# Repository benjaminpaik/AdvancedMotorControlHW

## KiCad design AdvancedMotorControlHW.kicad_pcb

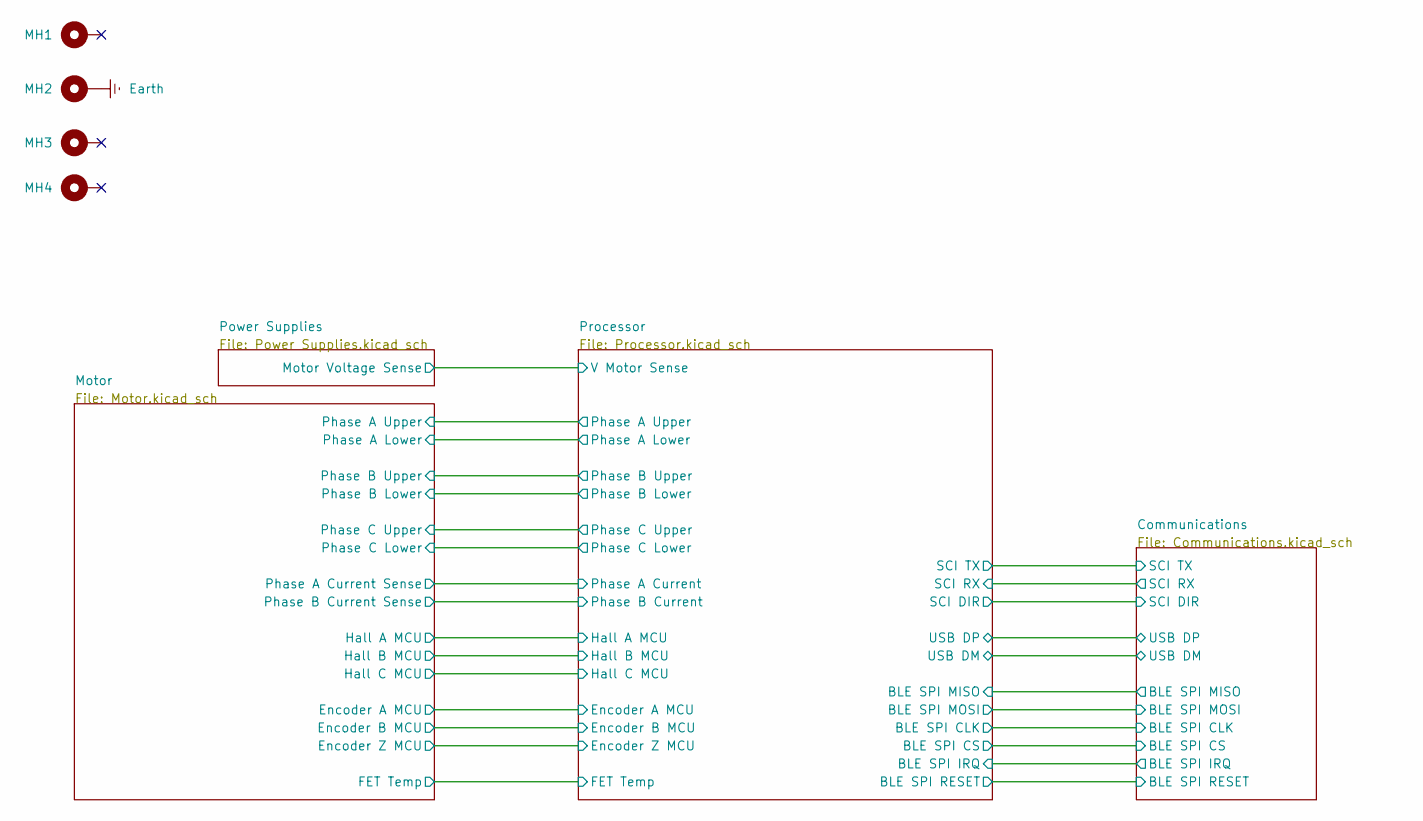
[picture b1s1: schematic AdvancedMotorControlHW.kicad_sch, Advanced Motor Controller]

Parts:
MH1, MH3, MH4: MountingHole; MountingHole_3.2mm_M3_Pad; Manufacturer Part Number 3480
MH2: MountingHole_Pad; MountingHole_3.2mm_M3_Pad; Manufacturer Part Number 3480

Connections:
Earth: MH2.1; also elsewhere on the board

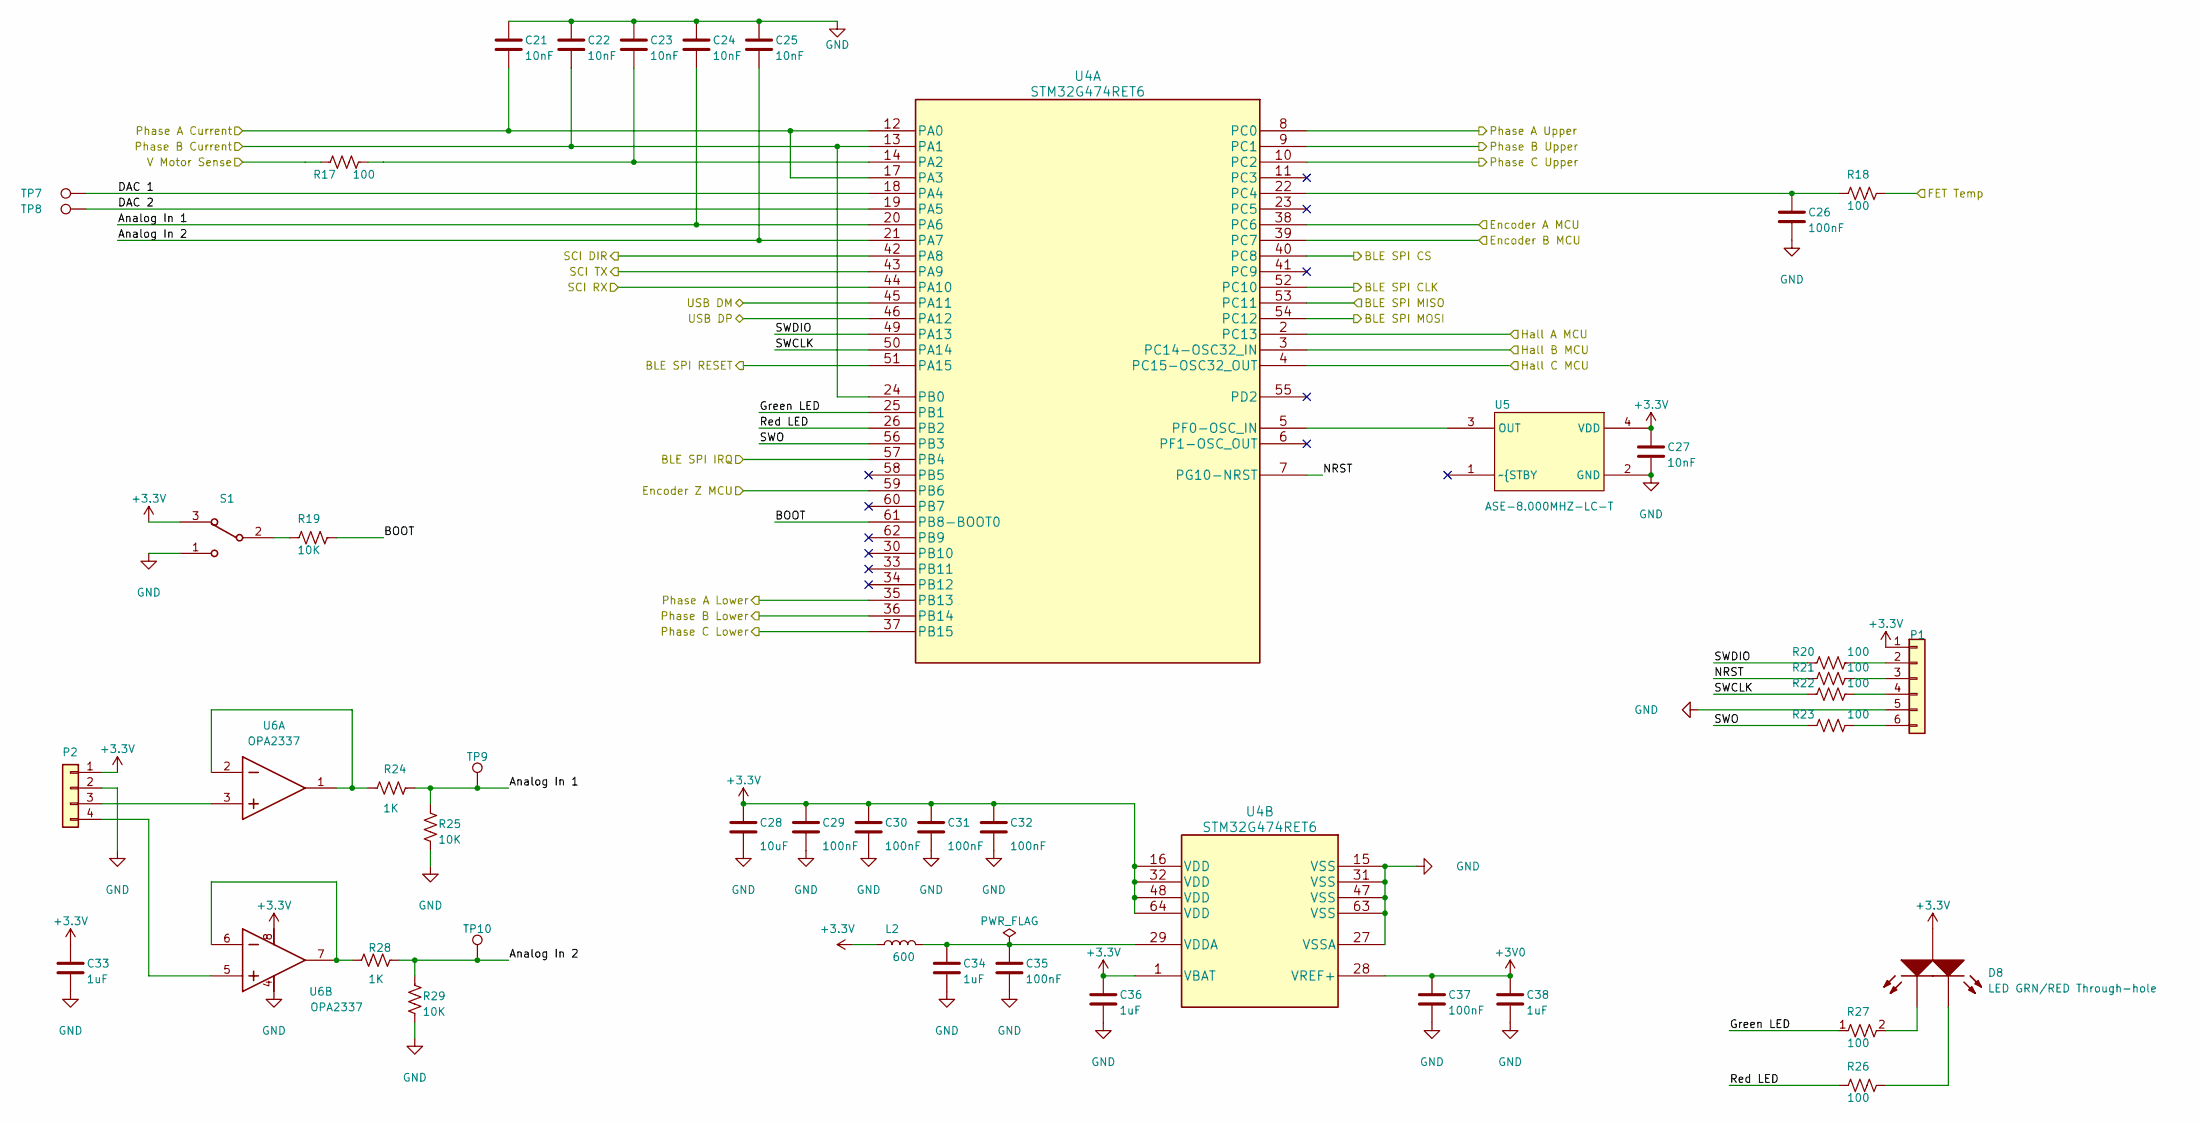
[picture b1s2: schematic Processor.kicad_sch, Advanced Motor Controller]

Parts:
C21, C22, C23, C24, C25, C27: 10nF; C_0603_1608Metric; Manufacturer Part Number CL10B103KB8NCNC
C26, C29, C30, C31, C32, C35, C37: 100nF; C_0603_1608Metric; Manufacturer Part Number 06035G104ZAT2A
C28: 10uF; C_1206_3216Metric; Manufacturer Part Number GRT31CR61H106ME01L
C33, C34, C36, C38: 1uF; C_0603_1608Metric; Manufacturer Part Number CL10A105KA8NNNC
D8: LED GRN/RED Through-hole; LED_D5.0mm-3; Manufacturer Part Number SSL-LX3059IGW-CA
L2: 600; L_0603_1608Metric; Manufacturer Part Number 742792651
P1: TC2030-MCP
P2: MOLEX RIGHT ANGLE HDR1X4; Manufacturer Part Number 0022057048
R17, R18, R20, R21, R22, R23, R26, R27: 100; R_0603_1608Metric; Manufacturer Part Number RC0603FR-07100RL
R19, R25, R29: 10K; R_0805_2012Metric; Manufacturer Part Number RR1220P-103-D
R24, R28: 1K; R_0603_1608Metric; Manufacturer Part Number RR0816P-102-D
S1: JS102011SAQN; Manufacturer Part Number JS102011SAQN
TP7, TP8, TP9, TP10: TestPoint; Manufacturer Part Number 5003
U4: STM32G474RET6; LQFP-64_10x10mm_P0.5mm; Manufacturer Part Number STM32G474RET6
U5: ASE-8.000MHZ-LC-T; Crystal_SMD_Abracon_ABM8G-4Pin_3.2x2.5mm; Manufacturer Part Number ASE-8.000MHZ-LC-T
U6: OPA2337; SOT-23-8; Manufacturer Part Number OPA2337EA/3K

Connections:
+3.3V: C27.1, C28.1, C29.1, C30.1, C31.1, C32.1, C33.1, C36.1, D8.2 (CA), L2.1, P1.1, P2.1, S1.3, U4.1 (VBAT), U4.16 (VDD), U4.32 (VDD), U4.48 (VDD), U4.64 (VDD), U5.4 (VDD), U6.8; also elsewhere on the board
+3V0: C37.1, C38.1, U4.28 (VREF+); also elsewhere on the board
/Communications/BLE SPI CLK: U4.52 (PC10); also elsewhere on the board
/Communications/BLE SPI CS: U4.40 (PC8); also elsewhere on the board
/Communications/BLE SPI IRQ: U4.57 (PB4); also elsewhere on the board
/Communications/BLE SPI MISO: U4.53 (PC11); also elsewhere on the board
/Communications/BLE SPI MOSI: U4.54 (PC12); also elsewhere on the board
/Communications/RESETN: U4.51 (PA15); also elsewhere on the board
/Communications/SCI DIR: U4.42 (PA8); also elsewhere on the board
/Communications/SCI RX: U4.44 (PA10); also elsewhere on the board
/Communications/SCI TX: U4.43 (PA9); also elsewhere on the board
/Communications/USB DM: U4.45 (PA11); also elsewhere on the board
/Communications/USB DP: U4.46 (PA12); also elsewhere on the board
/Motor/Encoder A MCU: U4.38 (PC6); also elsewhere on the board
/Motor/Encoder B MCU: U4.39 (PC7); also elsewhere on the board
/Motor/Encoder Z MCU: U4.59 (PB6); also elsewhere on the board
/Motor/FET Temp: R18.2; also elsewhere on the board
/Motor/Hall A MCU: U4.2 (PC13); also elsewhere on the board
/Motor/Hall B MCU: U4.3 (PC14-OSC32_IN); also elsewhere on the board
/Motor/Hall C MCU: U4.4 (PC15-OSC32_OUT); also elsewhere on the board
/Motor/Phase A Current Sense: C21.2, U4.12 (PA0), U4.17 (PA3); also elsewhere on the board
/Motor/Phase A Lower: U4.35 (PB13); also elsewhere on the board
/Motor/Phase A Upper: U4.8 (PC0); also elsewhere on the board
/Motor/Phase B Current Sense: C22.2, U4.13 (PA1), U4.24 (PB0); also elsewhere on the board
/Motor/Phase B Lower: U4.36 (PB14); also elsewhere on the board
/Motor/Phase B Upper: U4.9 (PC1); also elsewhere on the board
/Motor/Phase C Lower: U4.37 (PB15); also elsewhere on the board
/Motor/Phase C Upper: U4.10 (PC2); also elsewhere on the board
/Power Supplies/Motor Voltage Sense: R17.1; also elsewhere on the board
/Processor/Analog In 1: C24.2, R24.2, R25.2, TP9.1, U4.20 (PA6)
/Processor/Analog In 2: C25.2, R28.1, R29.2, TP10.1, U4.21 (PA7)
/Processor/BOOT: R19.2, U4.61 (PB8-BOOT0)
/Processor/DAC 1: TP7.1, U4.18 (PA4)
/Processor/DAC 2: TP8.1, U4.19 (PA5)
/Processor/Green LED: R27.1, U4.25 (PB1)
/Processor/NRST: R21.1, U4.7 (PG10-NRST)
/Processor/Red LED: R26.1, U4.26 (PB2)
/Processor/SWCLK: R22.1, U4.50 (PA14)
/Processor/SWDIO: R20.1, U4.49 (PA13)
/Processor/SWO: R23.1, U4.56 (PB3)
GND: C21.1, C22.1, C23.1, C24.1, C25.1, C26.2, C27.2, C28.2, C29.2, C30.2, C31.2, C32.2, C33.2, C34.2, C35.2, C36.2, C37.2, C38.2, P1.5, P2.2, R25.1, R29.1, S1.1, U4.15 (VSS), U4.27 (VSSA), U4.31 (VSS), U4.47 (VSS), U4.63 (VSS), U5.2 (GND), U6.4; also elsewhere on the board
unnamed: C34.1, C35.1, L2.2, U4.29 (VDDA)
unnamed: D8.3 (GK), R27.2
unnamed: D8.1 (RK), R26.2
unnamed: P1.2, R20.2
unnamed: P1.3, R21.2
unnamed: P1.4, R22.2
unnamed: P1.6, R23.2
unnamed: P2.3, U6.3 (IN_A+)
unnamed: P2.4, U6.5 (IN_B+)
unnamed: R19.1, S1.2
unnamed: C23.2, R17.2, U4.14 (PA2)
unnamed: C26.1, R18.1, U4.22 (PC4)
unnamed: U4.5 (PF0-OSC_IN), U5.3 (OUT)
unnamed: R24.1, U6.1 (OUT_A), U6.2 (IN_A-)
unnamed: R28.2, U6.6 (IN_B-), U6.7 (OUT_B)

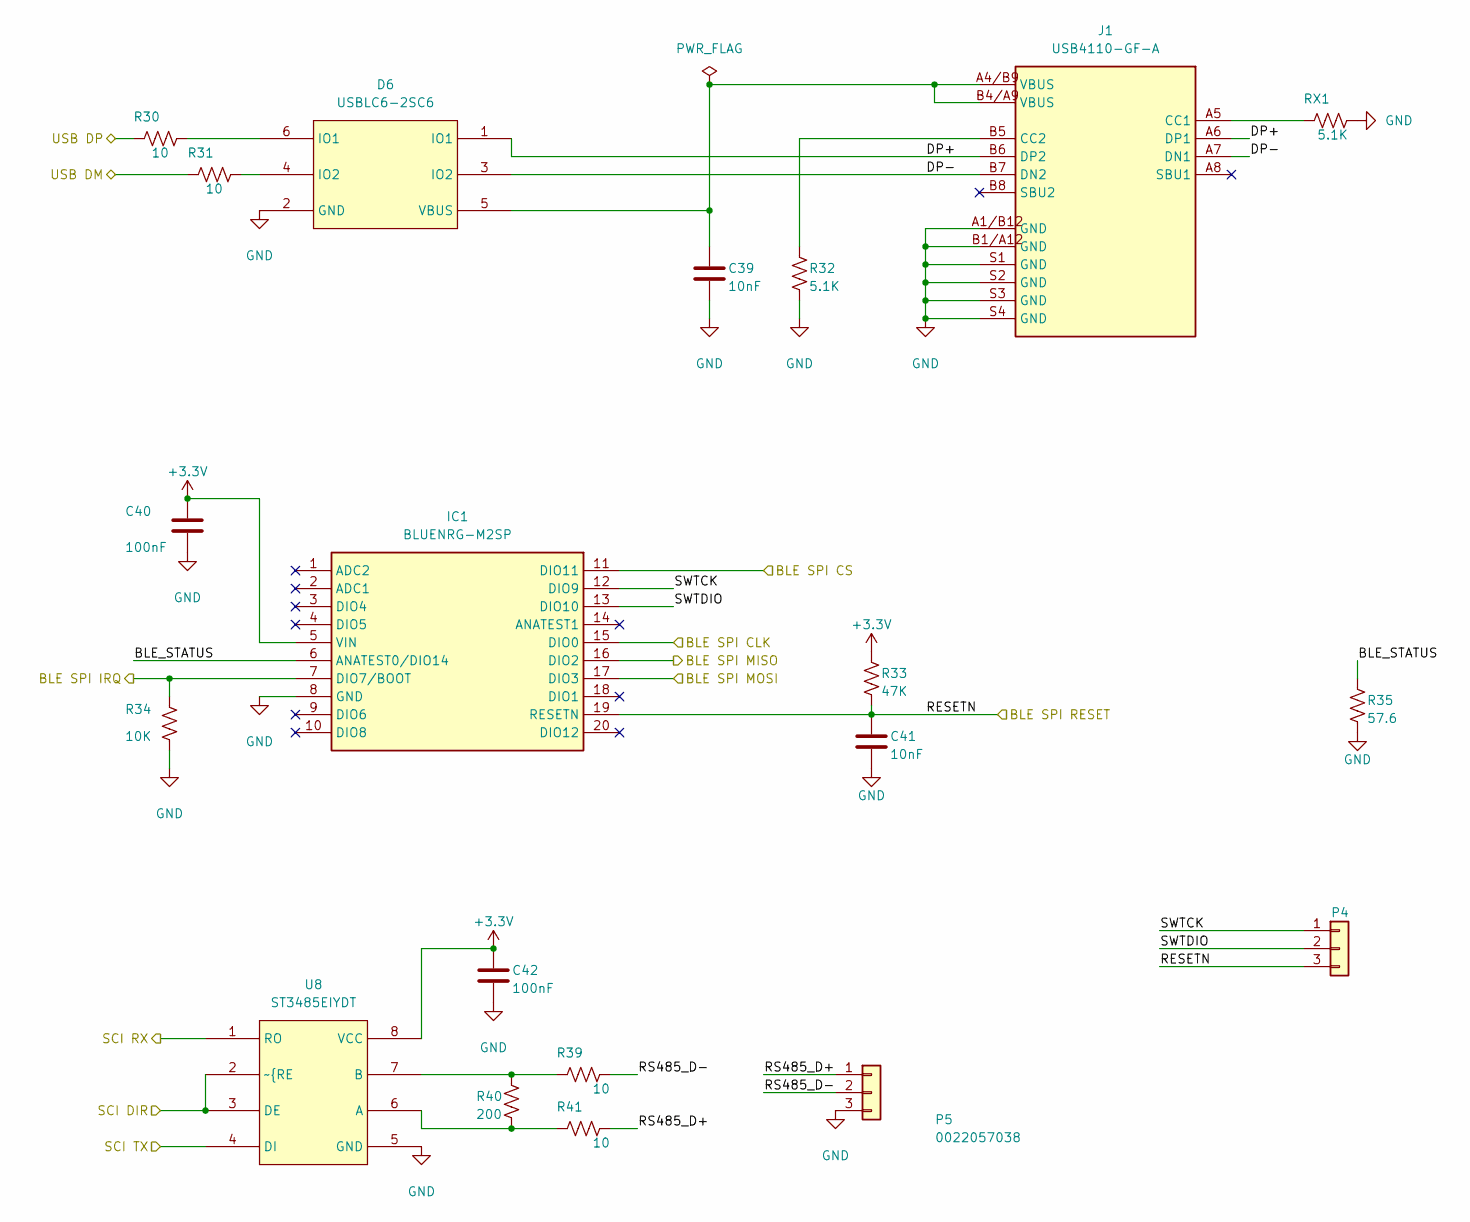
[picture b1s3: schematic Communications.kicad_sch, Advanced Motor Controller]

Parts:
C39, C41: 10nF; C_0603_1608Metric; Manufacturer Part Number CL10B103KB8NCNC
C40, C42: 100nF; C_0603_1608Metric; Manufacturer Part Number 06035G104ZAT2A
D6: USBLC6-2SC6; SOT-23-6; Manufacturer Part Number USBLC6-2SC6
IC1: BLUENRG-M2SP; BLUENRGM2SP; Manufacturer Part Number BLUENRG-M2SP
J1: USB4110-GF-A; USB-C Type 2.0 Connector; Manufacturer Part Number USB4110-GF-A
P4: 0022057038; PinHeader_1x03_P2.54mm_Vertical; Manufacturer Part Number 0022057038
P5: 0022057038; MOLEX RIGHT ANGLE HDR1X3; Manufacturer Part Number 0022057038
R30, R31, R39, R41: 10; R_0603_1608Metric; Manufacturer Part Number CRCW060310R0JNEAC
R32: 5.1K; R_0603_1608Metric; Manufacturer Part Number RMCF0603FT5K10
R33: 47K; R_0603_1608Metric; Manufacturer Part Number RT0603FRD0747KL
R34: 10K; R_0805_2012Metric; Manufacturer Part Number RR1220P-103-D
R35: 57.6; R_0805_2012Metric; Manufacturer Part Number RR1220P-103-D
R40: 200; R_0603_1608Metric; Manufacturer Part Number ERA-3AEB201V
RX1: 5.1K; R_0603_1608Metric; Manufacturer Part Number RMCF0603FT5K10
U8: ST3485EIYDT; SO-8_3.9x4.9mm_P1.27mm; Manufacturer Part Number ST3485EIYDT

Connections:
+3.3V: C40.1, C42.1, IC1.5 (VIN), R33.1, U8.8 (VCC); also elsewhere on the board
/Communications/BLE SPI CLK: IC1.15 (DIO0); also elsewhere on the board
/Communications/BLE SPI CS: IC1.11 (DIO11); also elsewhere on the board
/Communications/BLE SPI IRQ: IC1.7 (DIO7/BOOT), R34.1; also elsewhere on the board
/Communications/BLE SPI MISO: IC1.16 (DIO2); also elsewhere on the board
/Communications/BLE SPI MOSI: IC1.17 (DIO3); also elsewhere on the board
/Communications/BLE_STATUS: IC1.6 (ANATEST0/DIO14), R35.1
/Communications/DP+: D6.1 (IO1), J1.A6 (DP1), J1.B6 (DP2)
/Communications/DP-: D6.3 (IO2), J1.A7 (DN1), J1.B7 (DN2)
/Communications/RESETN: C41.1, IC1.19 (RESETN), P4.3, R33.2; also elsewhere on the board
/Communications/RS485_D+: P5.1, R41.2
/Communications/RS485_D-: P5.2, R39.2
/Communications/SCI DIR: U8.2 (~{RE), U8.3 (DE); also elsewhere on the board
/Communications/SCI RX: U8.1 (RO); also elsewhere on the board
/Communications/SCI TX: U8.4 (DI); also elsewhere on the board
/Communications/SWTCK: IC1.12 (DIO9), P4.1
/Communications/SWTDIO: IC1.13 (DIO10), P4.2
/Communications/USB DM: R31.1; also elsewhere on the board
/Communications/USB DP: R30.1; also elsewhere on the board
GND: C39.2, C40.2, C41.2, C42.2, D6.2 (GND), IC1.8 (GND), J1.A1/B12 (GND), J1.B1/A12 (GND), J1.S1 (GND), J1.S2 (GND), J1.S3 (GND), J1.S4 (GND), P5.3, R32.2, R34.2, R35.2, RX1.2, U8.5 (GND); also elsewhere on the board
unnamed: C39.1, D6.5 (VBUS), J1.A4/B9 (VBUS), J1.B4/A9 (VBUS)
unnamed: D6.6 (IO1), R30.2
unnamed: D6.4 (IO2), R31.2
unnamed: J1.A5 (CC1), RX1.1
unnamed: J1.B5 (CC2), R32.1
unnamed: R40.2, R41.1, U8.6 (A)
unnamed: R39.1, R40.1, U8.7 (B)

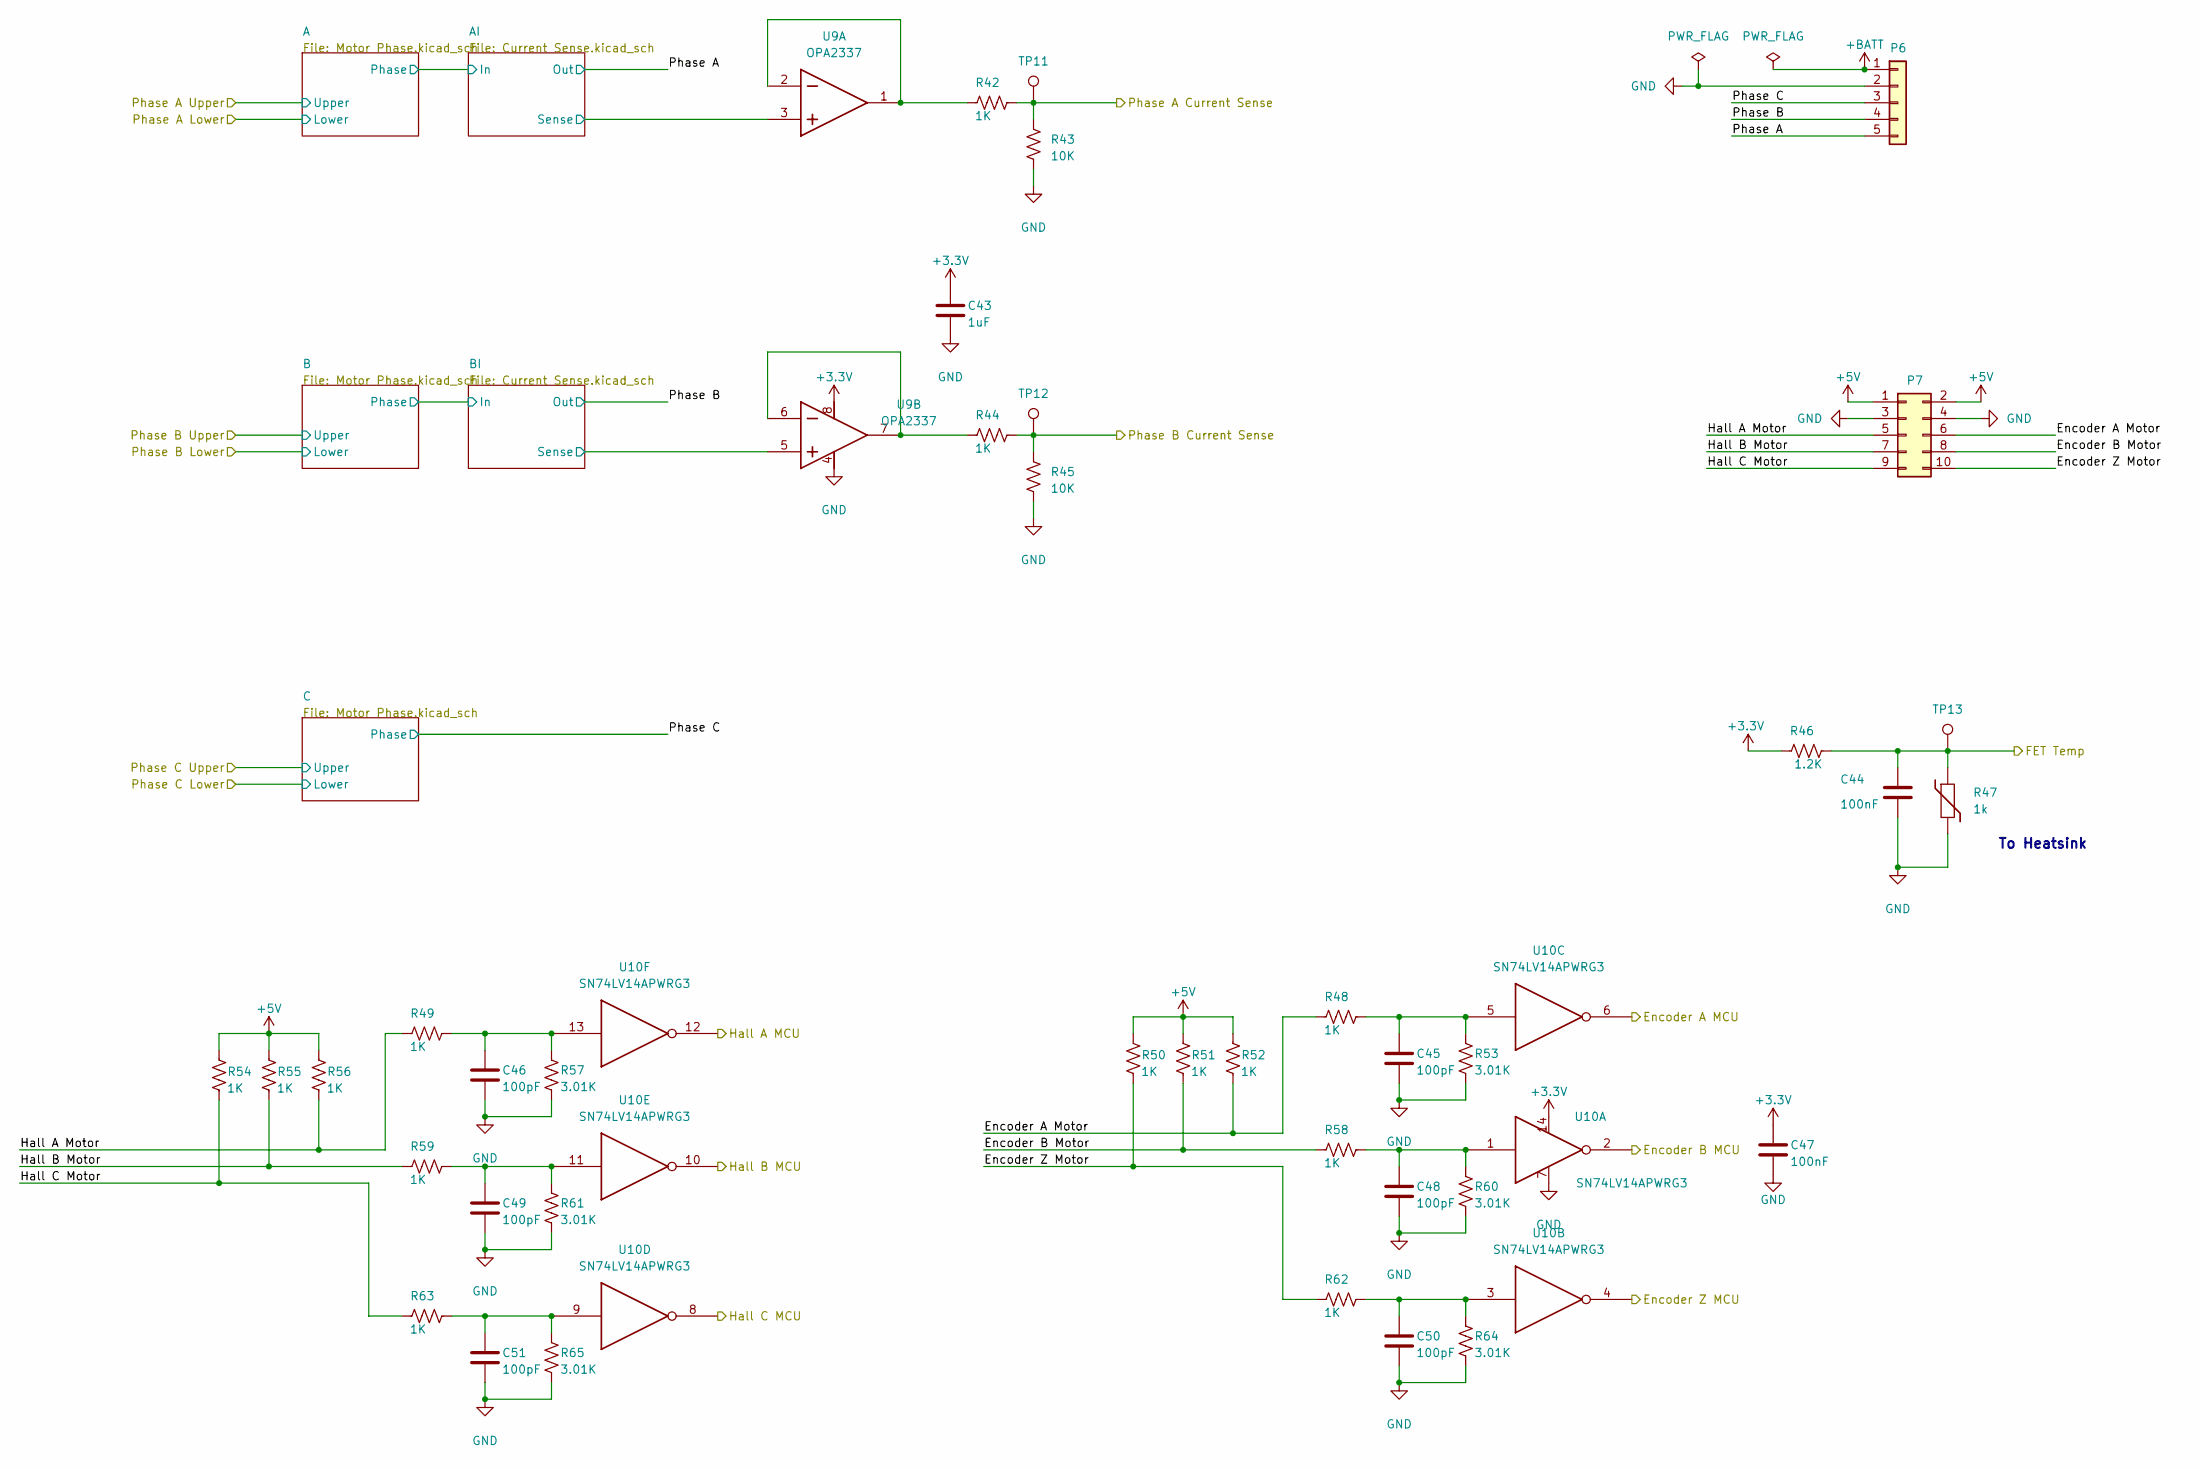
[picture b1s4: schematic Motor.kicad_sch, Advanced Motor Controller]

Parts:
C43: 1uF; C_0603_1608Metric; Manufacturer Part Number CL10A105KA8NNNC
C44, C47: 100nF; C_0603_1608Metric; Manufacturer Part Number 06035G104ZAT2A
C45, C46, C48, C49, C50, C51: 100pF; C_0603_1608Metric; Manufacturer Part Number CC0603JRNPO9BN101
P6: TERMBLK_200_5; Manufacturer Part Number 796638-5
P7: MOLEX RIGHT ANGLE HDR2X5; Manufacturer Part Number 0901303110
R42, R44, R48, R49, R50, R51, R52, R54, R55, R56, R58, R59, R62, R63: 1K; R_0603_1608Metric; Manufacturer Part Number RR0816P-102-D
R43, R45: 10K; R_0805_2012Metric; Manufacturer Part Number RR1220P-103-D
R46: 1.2K; R_0603_1608Metric; Manufacturer Part Number ERA-3ARB122V
R47: 1k; PinHeader_1x02_P2.54mm_Vertical; Manufacturer Part Number 32208572
R53, R57, R60, R61, R64, R65: 3.01K; R_0603_1608Metric; Manufacturer Part Number RC0603FR-073K01L
TP11, TP12, TP13: TestPoint; Manufacturer Part Number 5003
U9: OPA2337; SOT-23-8; Manufacturer Part Number OPA2337EA/3K
U10: SN74LV14APWRG3; TSSOP-14_4.4x5mm_P0.65mm; Manufacturer Part Number SN74LV14APWRG3

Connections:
+3.3V: C43.1, C47.1, R46.1, U9.8, U10.14 (VCC); also elsewhere on the board
+5V: P7.1, P7.2, R50.2, R51.2, R52.2, R54.2, R55.2, R56.2; also elsewhere on the board
+BATT: P6.1; also elsewhere on the board
/Motor/AI/Sense: U9.3 (IN_A+); also elsewhere on the board
/Motor/BI/Sense: U9.5 (IN_B+); also elsewhere on the board
/Motor/Encoder A MCU: U10.6 (O); also elsewhere on the board
/Motor/Encoder A Motor: P7.6, R48.1, R52.1
/Motor/Encoder B MCU: U10.2 (O); also elsewhere on the board
/Motor/Encoder B Motor: P7.8, R51.1, R58.1
/Motor/Encoder Z MCU: U10.4 (O); also elsewhere on the board
/Motor/Encoder Z Motor: P7.10, R50.1, R62.1
/Motor/FET Temp: C44.1, R46.2, R47.1, TP13.1; also elsewhere on the board
/Motor/Hall A MCU: U10.12 (O); also elsewhere on the board
/Motor/Hall A Motor: P7.5, R49.1, R56.1
/Motor/Hall B MCU: U10.10 (O); also elsewhere on the board
/Motor/Hall B Motor: P7.7, R55.1, R59.1
/Motor/Hall C MCU: U10.8 (O); also elsewhere on the board
/Motor/Hall C Motor: P7.9, R54.1, R63.1
/Motor/Phase A: P6.5; also elsewhere on the board
/Motor/Phase A Current Sense: R42.2, R43.1, TP11.1; also elsewhere on the board
/Motor/Phase B: P6.4; also elsewhere on the board
/Motor/Phase B Current Sense: R44.2, R45.1, TP12.1; also elsewhere on the board
/Motor/Phase C: P6.3; also elsewhere on the board
GND: C43.2, C44.2, C45.2, C46.2, C47.2, C48.2, C49.2, C50.2, C51.2, P6.2, P7.3, P7.4, R43.2, R45.2, R47.2, R53.2, R57.2, R60.2, R61.2, R64.2, R65.2, U9.4, U10.7 (GND); also elsewhere on the board
unnamed: R42.1, U9.1 (OUT_A), U9.2 (IN_A-)
unnamed: R44.1, U9.6 (IN_B-), U9.7 (OUT_B)
unnamed: C48.1, R58.2, R60.1, U10.1 (I)
unnamed: C50.1, R62.2, R64.1, U10.3 (I)
unnamed: C45.1, R48.2, R53.1, U10.5 (I)
unnamed: C51.1, R63.2, R65.1, U10.9 (I)
unnamed: C49.1, R59.2, R61.1, U10.11 (I)
unnamed: C46.1, R49.2, R57.1, U10.13 (I)

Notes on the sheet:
To Heatsink

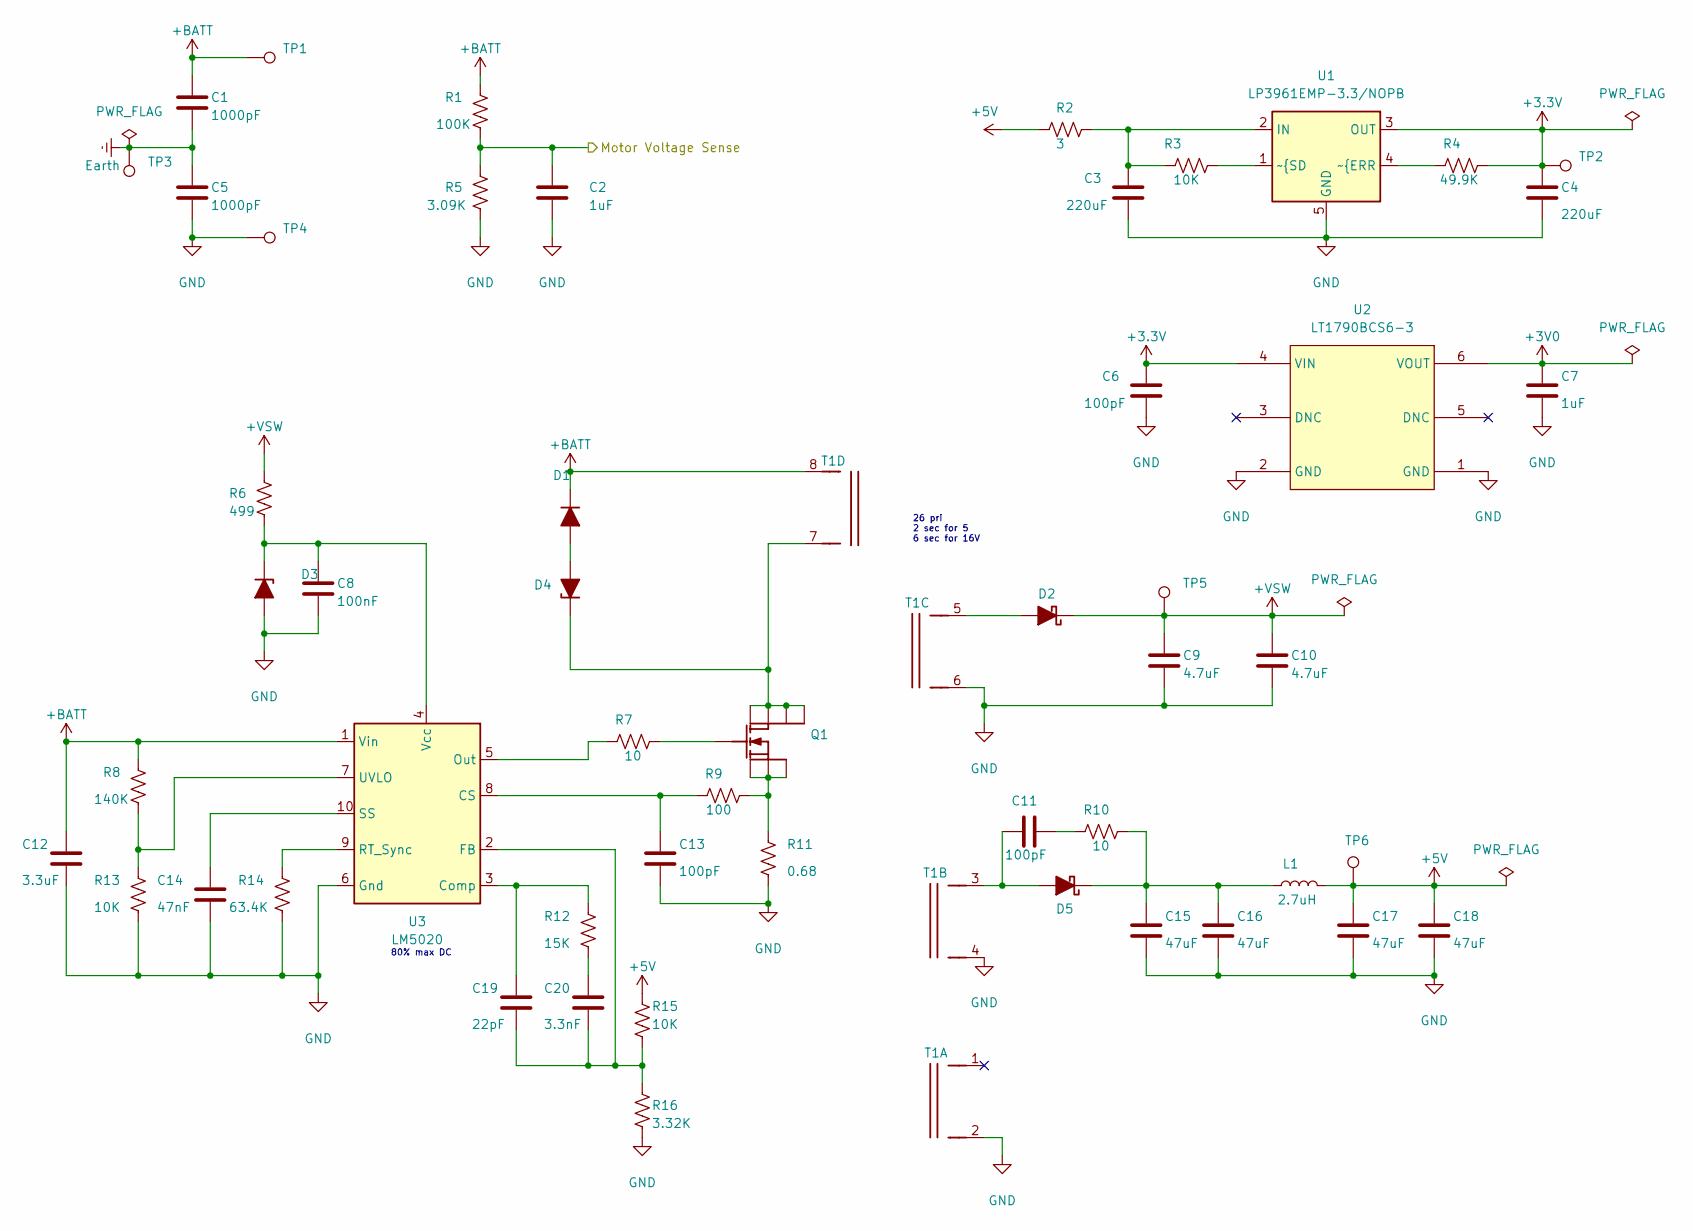
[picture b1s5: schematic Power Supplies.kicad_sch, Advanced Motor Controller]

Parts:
C1, C5: 1000pF; C_1206_3216Metric; Manufacturer Part Number C1206C102KCRACTU
C2, C7: 1uF; C_0603_1608Metric; Manufacturer Part Number CL10A105KA8NNNC
C3, C4: 220uF; CP_EIA-7343-31_Kemet-D; Manufacturer Part Number T495D227K010ATE125
C6, C11, C13: 100pF; C_0603_1608Metric; Manufacturer Part Number CC0603JRNPO9BN101
C8: 100nF; C_0603_1608Metric; Manufacturer Part Number 06035G104ZAT2A
C9, C10: 4.7uF; C_0805_2012Metric; Manufacturer Part Number CL21A475KACLRNC
C12: 3.3uF; C_2220_5650Metric; Manufacturer Part Number C5750X7R2A335K230KA
C14: 47nF; C_0805_2012Metric; Manufacturer Part Number CL21B473KCCWPNC
C15, C16, C17, C18: 47uF; C_1206_3216Metric; Manufacturer Part Number C3216X6S0J476M160AB
C19: 22pF; C_0603_1608Metric; Manufacturer Part Number CC0603JRNPO9BN220
C20: 3.3nF; C_0603_1608Metric; Manufacturer Part Number GRM1885C1H332JA01D
D1: SC-59; Manufacturer Part Number BAS21LT1G
D2: D_SOD-123; Manufacturer Part Number MBR0580-TP
D3: SC-59; Manufacturer Part Number BZX84C10-7-F
D4: D_SOD-123; Manufacturer Part Number MMSZ5268BT1G
D5: D_SOD-123; Manufacturer Part Number MBR0530T1G
L1: 2.7uH; 74404031027A; Manufacturer Part Number 74404031027A
Q1: SO-8_3.9x4.9mm_P1.27mm; Manufacturer Part Number SI4434DY-T1-E3
R1: 100K; R_0603_1608Metric; Manufacturer Part Number RR0816P-104-D
R2: 3; R_2512_6332Metric; Manufacturer Part Number RMCF2512JT3R00
R3, R13, R15: 10K; R_0805_2012Metric; Manufacturer Part Number RR1220P-103-D
R4: 49.9K; R_0603_1608Metric; Manufacturer Part Number RC0603FR-0749K9L
R5: 3.09K; R_0603_1608Metric; Manufacturer Part Number RT0603BRD073K09L
R6: 499; R_0603_1608Metric; Manufacturer Part Number RC0603FR-07499RL
R7: 10; R_0603_1608Metric; Manufacturer Part Number CRCW060310R0JNEAC
R8: 140K; R_0603_1608Metric; Manufacturer Part Number ERJ-3EKF1403V
R9: 100; R_0603_1608Metric; Manufacturer Part Number RC0603FR-07100RL
R10: 10; R_1210_3225Metric; Manufacturer Part Number CRCW121010R0JNEA
R11: 0.68; R_1206_3216Metric; Manufacturer Part Number RCWE1206R680FKEA
R12: 15K; R_0603_1608Metric; Manufacturer Part Number RC0603FR-0715KL
R14: 63.4K; R_0603_1608Metric; Manufacturer Part Number RC0603FR-0763K4L
R16: 3.32K; R_0603_1608Metric; Manufacturer Part Number RC0603FR-073K32L
T1: (no value)
TP1, TP2, TP3, TP4, TP5, TP6: TestPoint; Manufacturer Part Number 5003
U1: LP3961EMP-3.3/NOPB; SOT-223-5; Manufacturer Part Number LP3961EMP-3.3/NOPB
U2: LT1790BCS6-3; SOT-23-6; Manufacturer Part Number LT1790BCS6-3#TRMPBF
U3: LM5020; VSSOP-10_3x3mm_P0.5mm; Manufacturer Part Number LM5020MM-1/NOPB

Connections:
+3.3V: C4.1, C6.1, R4.2, TP2.1, U1.3 (OUT), U2.4 (VIN); also elsewhere on the board
+3V0: C7.1, U2.6 (VOUT); also elsewhere on the board
+5V: C17.1, C18.1, L1.2, R2.1, R15.1, TP6.1; also elsewhere on the board
+BATT: C1.1, C12.1, D1.1 (K), R1.1, R8.1, T1.8 (~{D), TP1.1, U3.1 (Vin); also elsewhere on the board
+VSW: C9.1, C10.1, D2.1 (K), R6.1, TP5.1; also elsewhere on the board
/Power Supplies/Motor Voltage Sense: C2.1, R1.2, R5.1; also elsewhere on the board
Earth: C1.2, C5.1, TP3.1; also elsewhere on the board
GND: C2.2, C3.2, C4.2, C5.2, C6.2, C7.2, C8.2, C9.2, C10.2, C12.2, C13.2, C14.2, C15.2, C16.2, C17.2, C18.2, D3.2 (A), R5.2, R11.2, R13.2, R14.2, R16.2, T1.2 (~{D), T1.4 (~{D), T1.6 (~{D), TP4.1, U1.5 (GND), U2.1 (GND), U2.2 (GND), U3.6 (Gnd); also elsewhere on the board
unnamed: C11.2, R10.1
unnamed: C20.1, R12.2
unnamed: D1.2 (A), D4.2 (A)
unnamed: D2.2 (A), T1.5 (D)
unnamed: C8.1, D3.1 (K), R6.2, U3.4 (Vcc)
unnamed: D4.1 (K), Q1.5 (D), Q1.6 (D), Q1.7 (D), Q1.8 (D), T1.7 (D)
unnamed: C11.1, D5.2 (A), T1.3 (D)
unnamed: C15.1, C16.1, D5.1 (K), L1.1, R10.2
unnamed: Q1.4 (G), R7.2
unnamed: Q1.1 (S), Q1.2 (S), Q1.3 (S), R9.2, R11.1
unnamed: C3.1, R2.2, R3.1, U1.2 (IN)
unnamed: R4.1, U1.4 (~{ERR)
unnamed: R3.2, U1.1 (~{SD)
unnamed: C13.1, R9.1, U3.8 (CS)
unnamed: C19.1, R12.1, U3.3 (Comp)
unnamed: C19.2, C20.2, R15.2, R16.1, U3.2 (FB)
unnamed: R7.1, U3.5 (Out)
unnamed: R14.1, U3.9 (RT_Sync)
unnamed: C14.1, U3.10 (SS)
unnamed: R8.2, R13.1, U3.7 (UVLO)

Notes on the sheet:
80% max DC
26 pri 2 sec for 5 6 sec for 16V

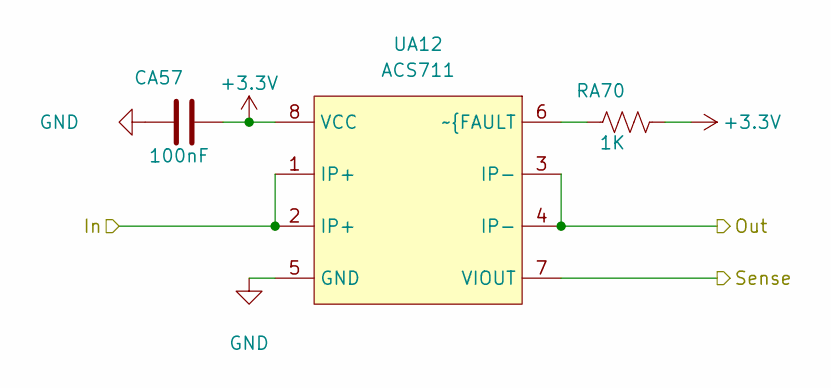
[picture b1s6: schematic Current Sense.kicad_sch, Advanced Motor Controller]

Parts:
CA57: 100nF; C_0603_1608Metric; Manufacturer Part Number 06035G104ZAT2A
RA70: 1K; R_0603_1608Metric; Manufacturer Part Number RR0816P-102-D
UA12: ACS711; SOIC-8_3.9x4.9mm_P1.27mm; Manufacturer Part Number ACS711ELCTR-12AB-T

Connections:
+3.3V: CA57.2, RA70.2, UA12.8 (VCC); also elsewhere on the board
/Motor/A/Phase: UA12.1 (IP+), UA12.2 (IP+); also elsewhere on the board
/Motor/AI/Sense: UA12.7 (VIOUT); also elsewhere on the board
/Motor/Phase A: UA12.3 (IP-), UA12.4 (IP-); also elsewhere on the board
GND: CA57.1, UA12.5 (GND); also elsewhere on the board
unnamed: RA70.1, UA12.6 (~{FAULT)

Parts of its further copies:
CB57: 100nF; C_0603_1608Metric; Manufacturer Part Number 06035G104ZAT2A
RB70: 1K; R_0603_1608Metric; Manufacturer Part Number RR0816P-102-D
UB12: ACS711; SOIC-8_3.9x4.9mm_P1.27mm; Manufacturer Part Number ACS711ELCTR-12AB-T

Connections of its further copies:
+3.3V: CB57.2, RB70.2, UB12.8 (VCC); also elsewhere on the board
/Motor/B/Phase: UB12.1 (IP+), UB12.2 (IP+); also elsewhere on the board
/Motor/BI/Sense: UB12.7 (VIOUT); also elsewhere on the board
/Motor/Phase B: UB12.3 (IP-), UB12.4 (IP-); also elsewhere on the board
GND: CB57.1, UB12.5 (GND); also elsewhere on the board
unnamed: RB70.1, UB12.6 (~{FAULT)
